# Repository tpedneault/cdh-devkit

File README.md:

# Define the color scheme
set colors(bg) "#ECEFF4"
set colors(bg_secondary) "#E5E9F0"
set colors(bg_highlight) "#D8DEE9"
set colors(fg) "#2E3440"
set colors(fg_secondary) "#3B4252"
set colors(fg_highlight) "#4C566A"
set colors(accent) "#5E81AC"
set colors(accent_hover) "#81A1C1"
set colors(accent_active) "#88C0D0"
set colors(border) "#D8DEE9"
set colors(border_focus) "#5E81AC"
set colors(border_disabled) "#E5E9F0"
set colors(button_bg) "#88C0D0"
set colors(button_fg) "#2E3440"
set colors(button_hover_bg) "#81A1C1"
set colors(button_active_bg) "#5E81AC"
set colors(input_bg) "#E5E9F0"
set colors(input_fg) "#2E3440"
set colors(input_border) "#D8DEE9"
set colors(alert_success_bg) "#A3BE8C"
set colors(alert_success_fg) "#2E3440"
set colors(alert_warning_bg) "#EBCB8B"
set colors(alert_warning_fg) "#2E3440"
set colors(alert_error_bg) "#BF616A"
set colors(alert_error_fg) "#2E3440"

# Create the main window
ttk::style configure TFrame -background $colors(bg)
ttk::style configure TLabel -background $colors(bg) -foreground $colors(fg)
ttk::style configure TButton -background $colors(button_bg) -foreground $colors(button_fg) -padding 6 -relief flat
ttk::style map TButton -background {active $colors(button_active_bg) pressed $colors(button_active_bg) focus $colors(accent_active)}
ttk::style configure TEntry -fieldbackground $colors(input_bg) -foreground $colors(input_fg) -relief solid -padding 6
ttk::style configure TCheckbutton -background $colors(bg) -foreground $colors(fg)
ttk::style configure TRadiobutton -background $colors(bg) -foreground $colors(fg)
ttk::style configure TCombobox -fieldbackground $colors(input_bg) -foreground $colors(input_fg) -relief solid -padding 6
ttk::style configure TSpinbox -fieldbackground $colors(input_bg) -foreground $colors(input_fg) -relief solid -padding 6
ttk::style configure TLabelframe -background $colors(bg) -foreground $colors(fg) -padding 10
ttk::style configure TLabelframe.Label -background $colors(bg) -foreground $colors(fg)
ttk::style configure Treeview -background $colors(bg_secondary) -foreground $colors(fg) -fieldbackground $colors(bg_secondary)
ttk::style configure Treeview.Heading -background $colors(bg_highlight) -foreground $colors(fg_highlight)
ttk::style configure TNotebook -background $colors(bg)
ttk::style configure TNotebook.Tab -background $colors(bg) -foreground $colors(fg)
ttk::style configure Horizontal.TScrollbar -background $colors(border)
ttk::style configure Vertical.TScrollbar -background $colors(border)
ttk::style configure TProgressbar -background $colors(accent)
ttk::style configure TSeparator -background $colors(border)
ttk::style configure TSizegrip -background $colors(bg_secondary)

# Create a sample GUI
ttk::frame .frame -padding "10 10 10 10"
grid .frame -column 0 -row 0 -sticky "nwes"

ttk::label .frame.label -text "Hello, World!"
grid .frame.label -column 0 -row 0 -pady 5

ttk::button .frame.button -text "Click Me"
grid .frame.button -column 0 -row 1 -pady 5

ttk::entry .frame.entry
grid .frame.entry -column 0 -row 2 -pady 5

ttk::checkbutton .frame.check -text "Check Me"
grid .frame.check -column 0 -row 3 -pady 5

ttk::radiobutton .frame.radio -text "Option 1" -value 1 -variable option
grid .frame.radio -column 0 -row 4 -pady 5

ttk::combobox .frame.combo -values {Option1 Option2 Option3}
grid .frame.combo -column 0 -row 5 -pady 5

ttk::spinbox .frame.spin -from 0 -to 10
grid .frame.spin -column 0 -row 6 -pady 5

ttk::labelframe .frame.labelframe -text "Group"
grid .frame.labelframe -column 0 -row 7 -pady 5

ttk::notebook .frame.notebook
grid .frame.notebook -column 0 -row 8 -pady 5

ttk::treeview .frame.tree -columns {Name Age}
grid .frame.tree -column 0 -row 9 -pady 5

ttk::progressbar .frame.progress
grid .frame.progress -column 0 -row 10 -pady 5

# Add contents to the labelframe
ttk::label .frame.labelframe.label -text "Inside Group"
grid .frame.labelframe.label -column 0 -row 0 -pady 5

# Add tabs to the notebook
ttk::frame .frame.notebook.tab1
ttk::frame .frame.notebook.tab2
.frame.notebook add .frame.notebook.tab1 -text "Tab 1"
.frame.notebook add .frame.notebook.tab2 -text "Tab 2"

# Add items to the treeview
.frame.tree heading Name -text "Name"
.frame.tree heading Age -text "Age"
.frame.tree insert {} end -values {"Alice" 30}
.frame.tree insert {} end -values {"Bob" 25}

# Start the main loop
tk::mainloop

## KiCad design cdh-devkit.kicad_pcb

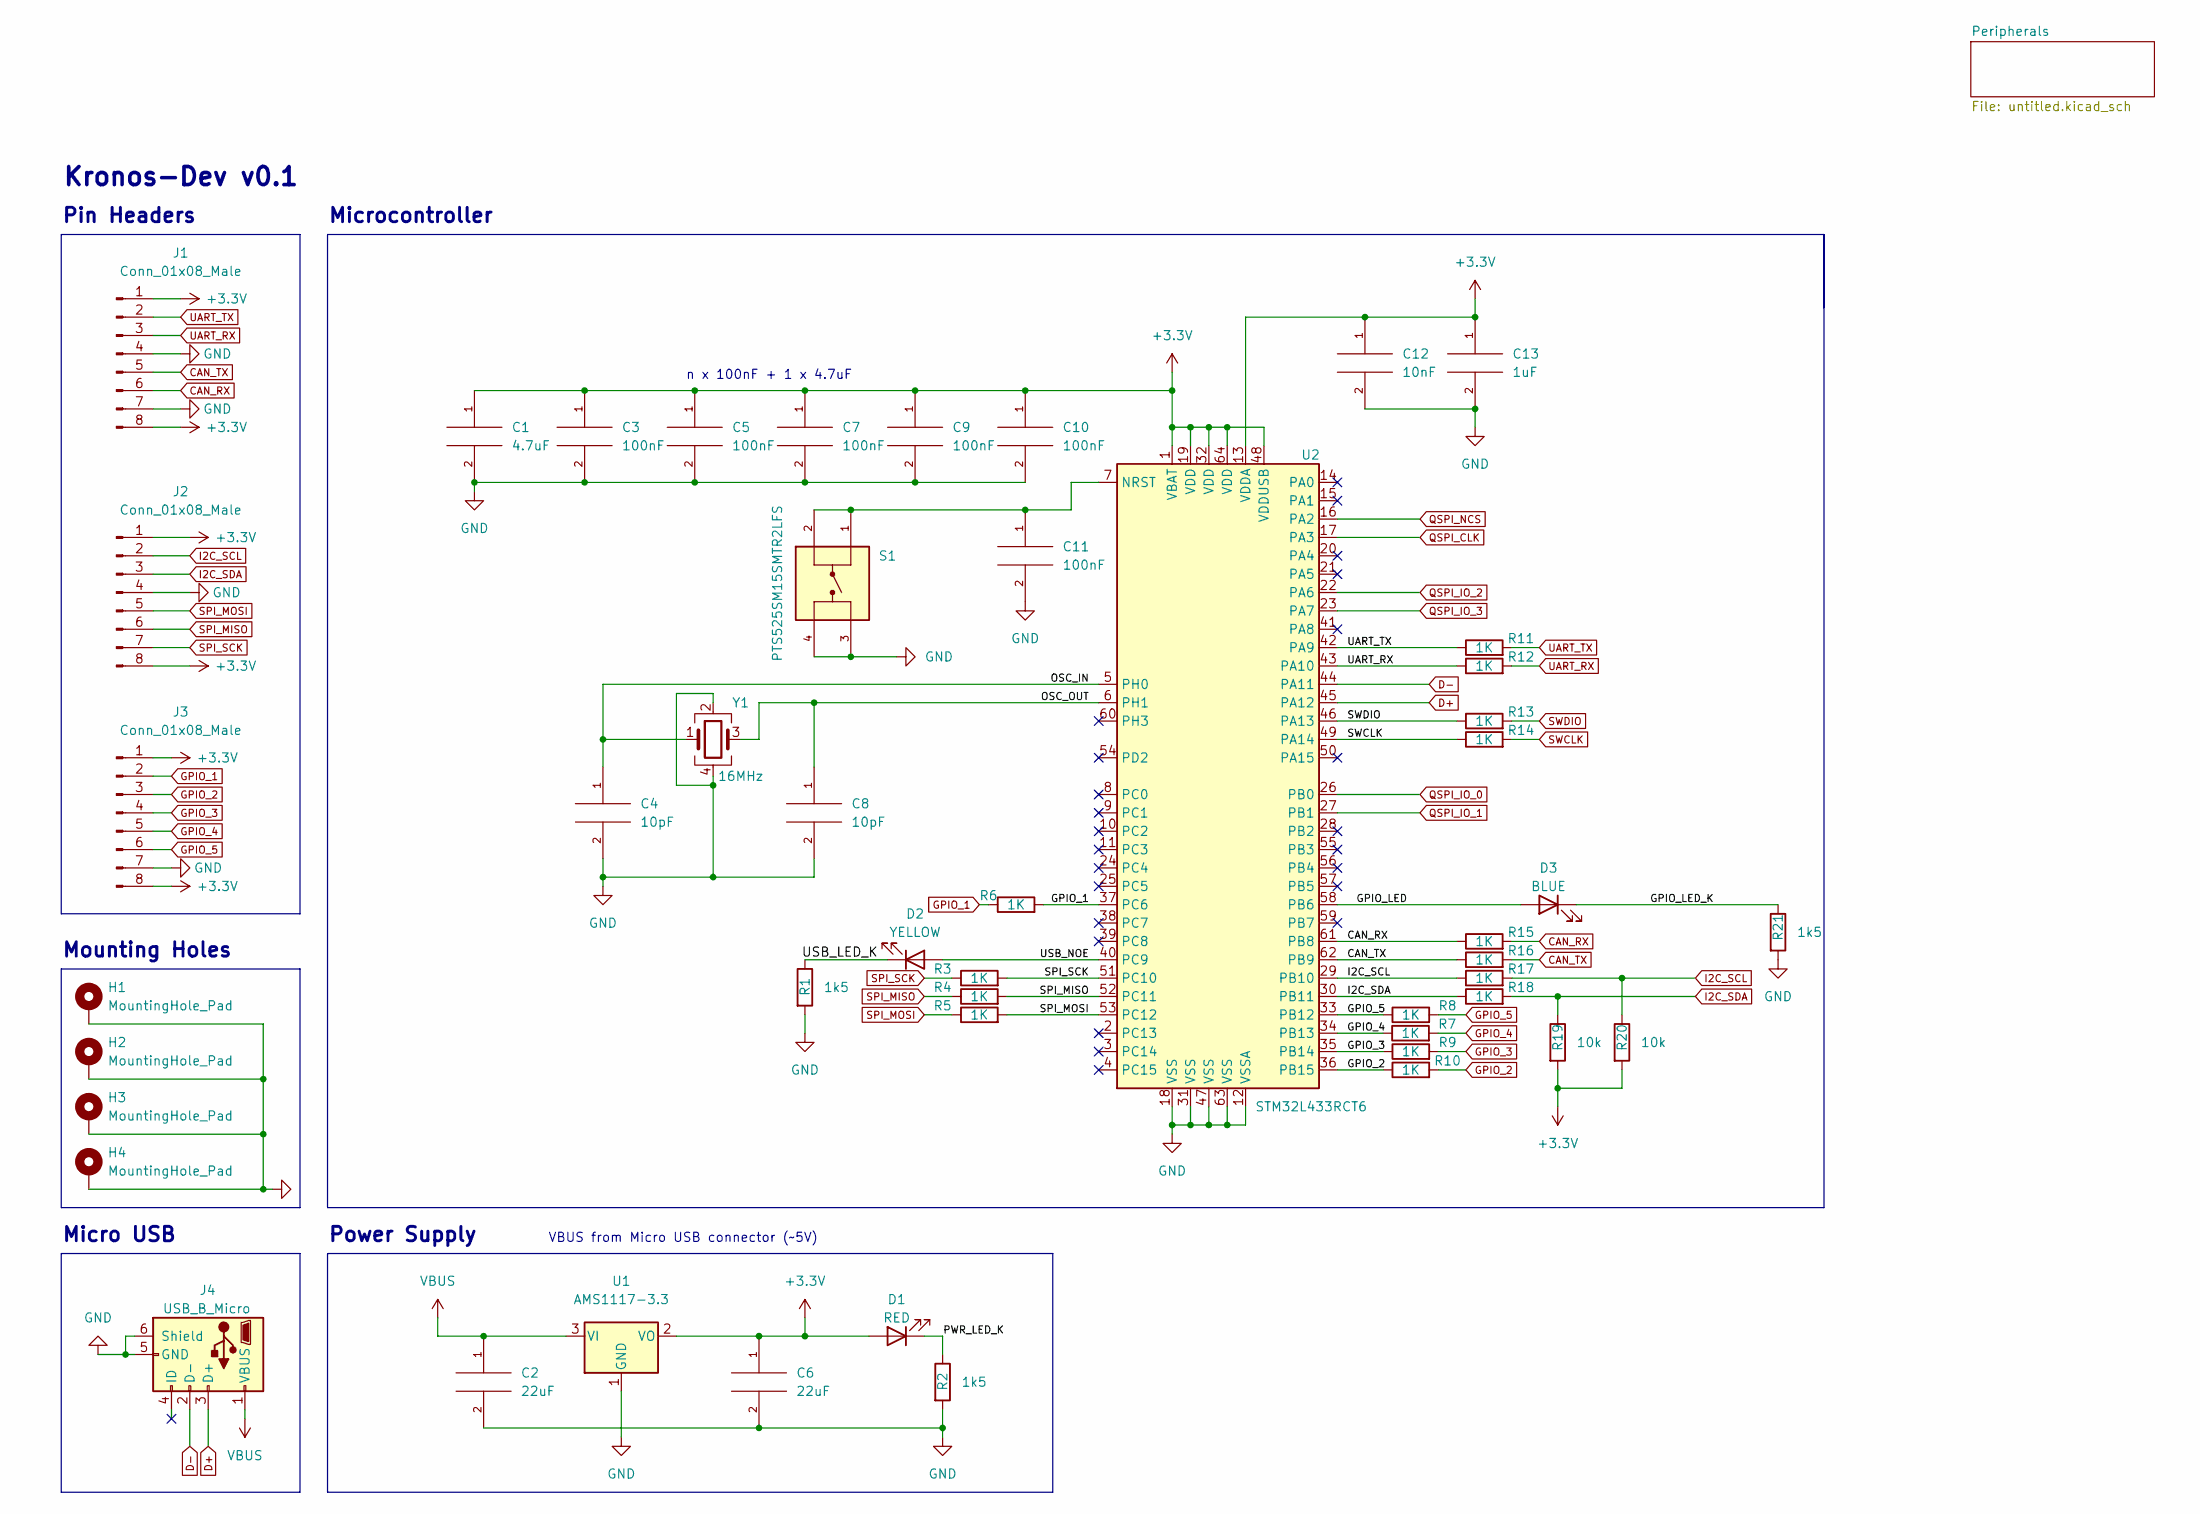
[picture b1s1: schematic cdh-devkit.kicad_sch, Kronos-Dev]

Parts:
C1: 4.7uF; C_0603_1608Metric
C2, C6: 22uF; C_0805_2012Metric
C3, C5, C7, C9, C10, C11: 100nF; C_0402_1005Metric
C4, C8: 10pF; C_0402_1005Metric
C12: 10nF; C_0402_1005Metric
C13: 1uF; C_0402_1005Metric
D1: RED; LED_0603_1608Metric
D2: YELLOW; LED_0603_1608Metric
D3: BLUE; LED_0603_1608Metric
H1, H2, H3, H4: MountingHole_Pad; MountingHole_2.2mm_M2_Pad
J1, J2, J3: Conn_01x08_Male; PinHeader_1x08_P2.54mm_Vertical
J4: USB_B_Micro; USB_Micro-B_Molex-105017-0001
R1, R2, R21: 1k5; R_0402_1005Metric
R3, R4, R5, R6, R7, R8, R9, R10, R11, R12, R13, R14, R15, R16, R17, R18: 1K; R_0402_1005Metric
R19, R20: 10k; R_0402_1005Metric
S1: PTS525SM15SMTR2LFS; SW_PTS525SM15SMTR2LFS; PARTREV NA
U1: AMS1117-3.3; SOT-223-3_TabPin2
U2: STM32L433RCT6; LQFP-64_10x10mm_P0.5mm
Y1: 16MHz; Crystal_SMD_3225-4Pin_3.2x2.5mm

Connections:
+3.3V: C1.1, C3.1, C5.1, C6.1, C7.1, C9.1, C10.1, C12.1, C13.1, D1.2 (A), J1.1, J1.8, J2.1, J2.8, J3.1, J3.8, R19.2, R20.2, U1.2 (VO), U2.1 (VBAT), U2.13 (VDDA), U2.19 (VDD), U2.32 (VDD), U2.48 (VDDUSB), U2.64 (VDD); also elsewhere on the board
/GPIO_LED: D3.2 (A), U2.58 (PB6)
/GPIO_LED_K: D3.1 (K), R21.1
/OSC_IN: C4.1, U2.5 (PH0), Y1.1
/OSC_OUT: C8.1, U2.6 (PH1), Y1.3
/PWR_LED_K: D1.1 (K), R2.1
/USB_LED_K: D2.1 (K), R1.1
/USB_NOE: D2.2 (A), U2.40 (PC9)
CAN_RX: J1.6, R15.1, R15.2, U2.61 (PB8); also elsewhere on the board
CAN_TX: J1.5, R16.1, R16.2, U2.62 (PB9); also elsewhere on the board
D+: J4.3 (D+), U2.45 (PA12); also elsewhere on the board
D-: J4.2 (D-), U2.44 (PA11); also elsewhere on the board
GND: C1.2, C2.2, C3.2, C4.2, C5.2, C6.2, C7.2, C8.2, C9.2, C10.2, C11.2, C12.2, C13.2, H1.1, H2.1, H3.1, H4.1, J1.4, J1.7, J2.4, J3.7, J4.5 (GND), J4.6 (Shield), R1.2, R2.2, R21.2, S1.3, S1.4, U1.1 (GND), U2.12 (VSSA), U2.18 (VSS), U2.31 (VSS), U2.47 (VSS), U2.63 (VSS), Y1.2, Y1.4; also elsewhere on the board
GPIO_1: J3.2, R6.1, R6.2, U2.37 (PC6); also elsewhere on the board
GPIO_2: J3.3, R10.1, R10.2, U2.36 (PB15); also elsewhere on the board
GPIO_3: J3.4, R9.1, R9.2, U2.35 (PB14); also elsewhere on the board
GPIO_4: J3.5, R7.1, R7.2, U2.34 (PB13); also elsewhere on the board
GPIO_5: J3.6, R8.1, R8.2, U2.33 (PB12); also elsewhere on the board
I2C_SCL: J2.2, R17.1, R17.2, R20.1, U2.29 (PB10); also elsewhere on the board
I2C_SDA: J2.3, R18.1, R18.2, R19.1, U2.30 (PB11); also elsewhere on the board
unnamed: C11.1, S1.1, S1.2, U2.7 (NRST)
QSPI_CLK: U2.17 (PA3); also elsewhere on the board
QSPI_IO_0: U2.26 (PB0); also elsewhere on the board
QSPI_IO_1: U2.27 (PB1); also elsewhere on the board
QSPI_IO_2: U2.22 (PA6); also elsewhere on the board
QSPI_IO_3: U2.23 (PA7); also elsewhere on the board
QSPI_NCS: U2.16 (PA2); also elsewhere on the board
SPI_MISO: J2.6, R4.1, R4.2, U2.52 (PC11); also elsewhere on the board
SPI_MOSI: J2.5, R5.1, R5.2, U2.53 (PC12); also elsewhere on the board
SPI_SCK: J2.7, R3.1, R3.2, U2.51 (PC10); also elsewhere on the board
SWCLK: R14.1, R14.2, U2.49 (PA14); also elsewhere on the board
SWDIO: R13.1, R13.2, U2.46 (PA13); also elsewhere on the board
UART_RX: J1.3, R12.1, R12.2, U2.43 (PA10); also elsewhere on the board
UART_TX: J1.2, R11.1, R11.2, U2.42 (PA9); also elsewhere on the board
VBUS: C2.1, J4.1 (VBUS), U1.3 (VI)

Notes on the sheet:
Power Supply
Pin Headers
VBUS from Micro USB connector (~5V)
Micro USB
Kronos-Dev v0.1
Microcontroller
Mounting Holes
n x 100nF + 1 x 4.7uF

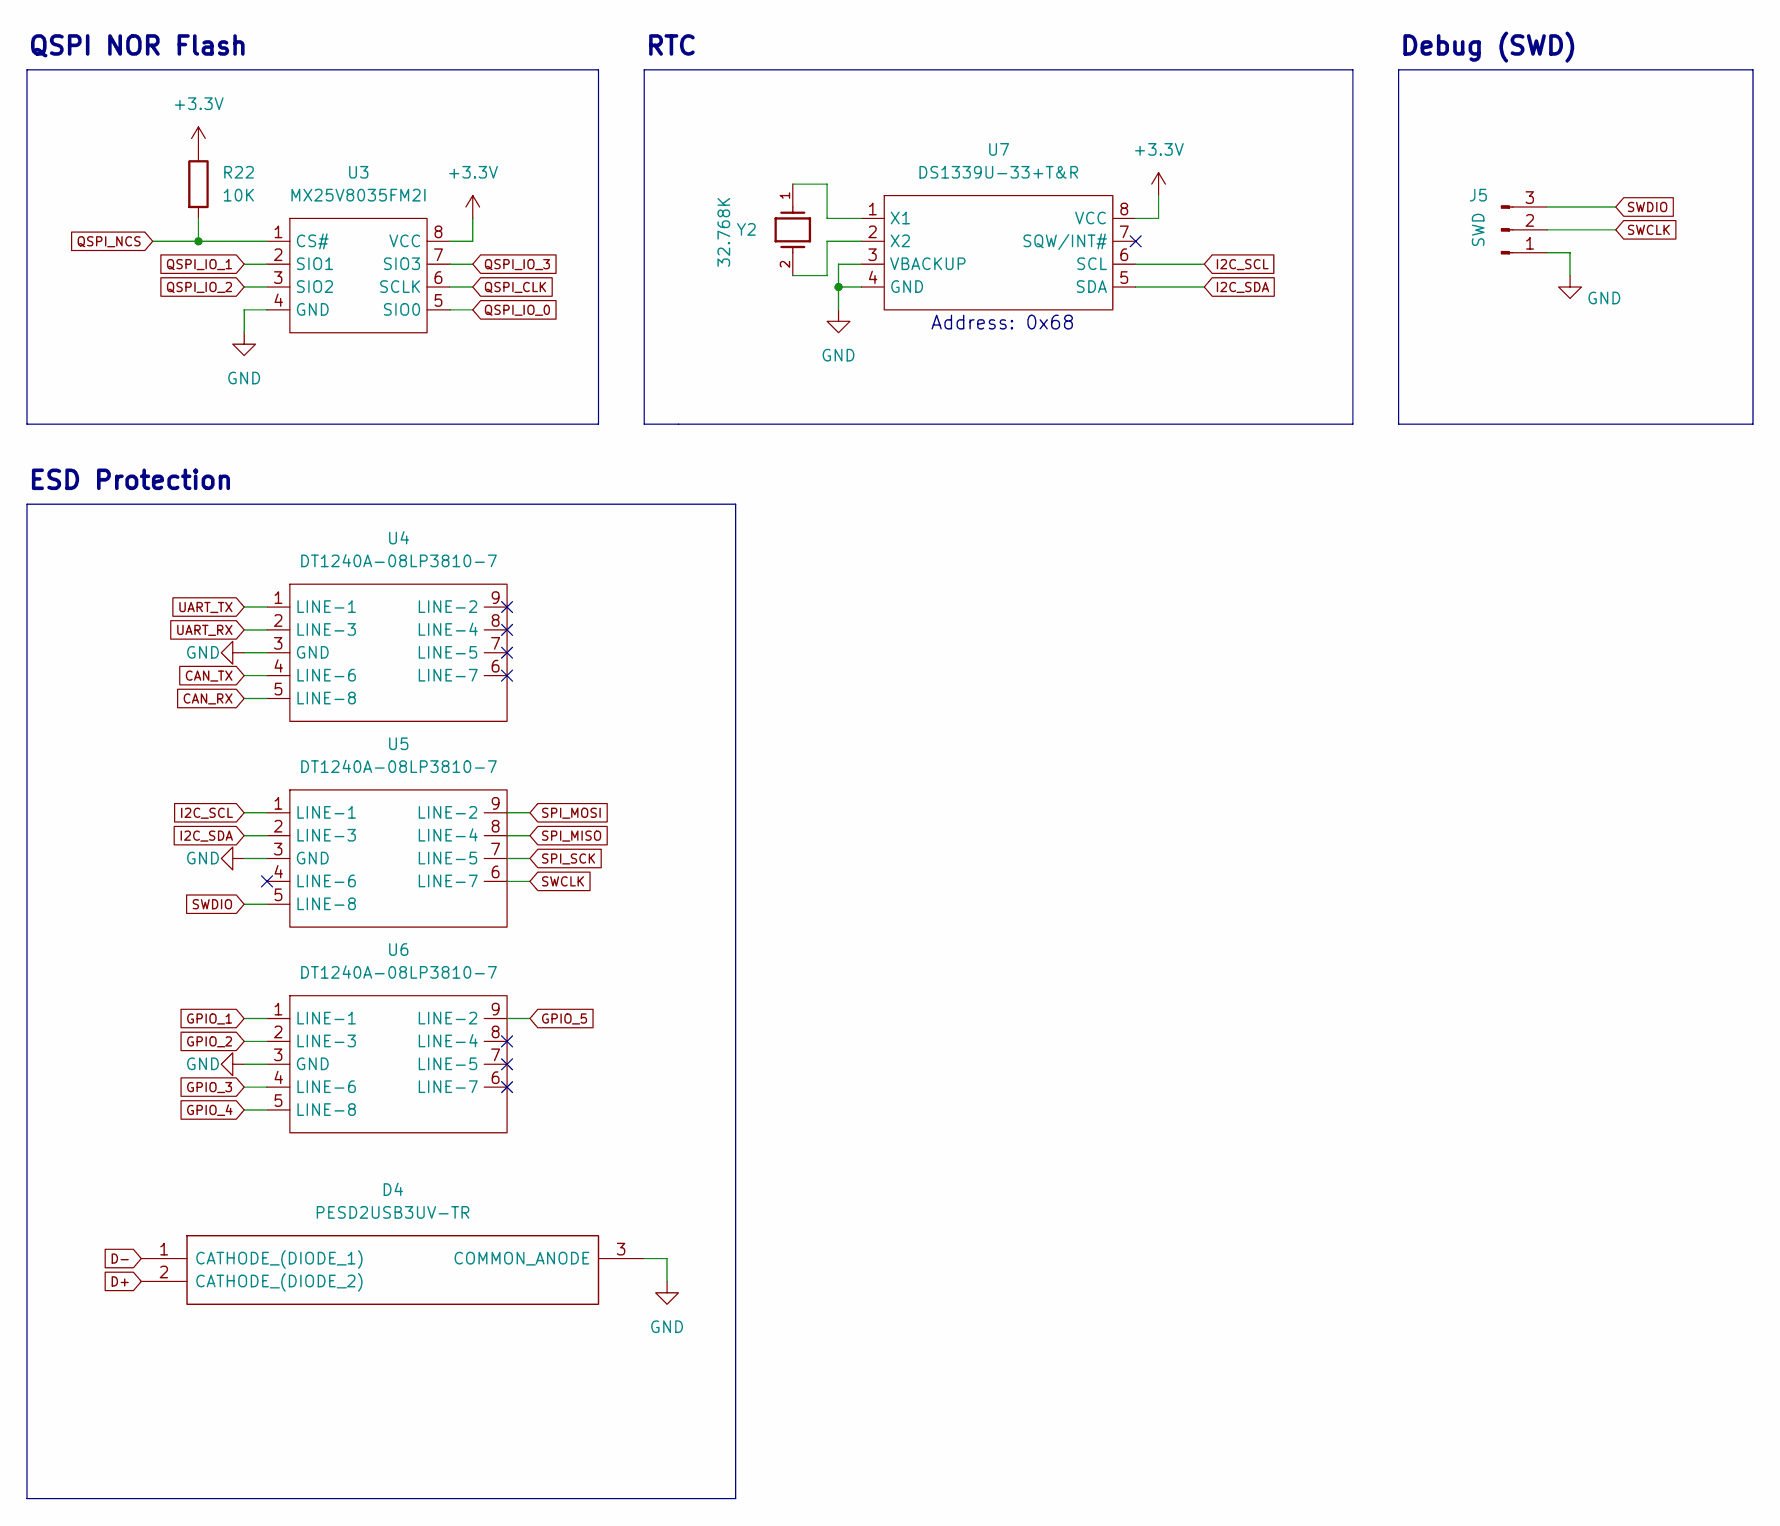
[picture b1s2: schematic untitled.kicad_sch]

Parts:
D4: PESD2USB3UV-TR; SOT95P230X110-3N; Mouser Part Number 771-PESD2USB3UV-TR
J5: SWD; PinHeader_1x03_P2.54mm_Vertical
R22: 10K; R_0603_1608Metric
U3: MX25V8035FM2I; SOIC127P790X216-8N
U4, U5, U6: DT1240A-08LP3810-7; TVS_824014883
U7: DS1339U-33+T&R; 21-0036K
Y2: 32.768K; XTAL_NX3215SA-32.768K-STD-MUA-14; PARTREV --

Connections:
+3.3V: R22.1, U3.8 (VCC), U7.8 (VCC); also elsewhere on the board
CAN_RX: U4.5 (LINE-8); also elsewhere on the board
CAN_TX: U4.4 (LINE-6); also elsewhere on the board
D+: D4.2 (CATHODE_(DIODE_2)); also elsewhere on the board
D-: D4.1 (CATHODE_(DIODE_1)); also elsewhere on the board
GND: D4.3 (COMMON_ANODE), J5.1, U3.4 (GND), U4.3 (GND), U5.3 (GND), U6.3 (GND), U7.3 (VBACKUP), U7.4 (GND); also elsewhere on the board
GPIO_1: U6.1 (LINE-1); also elsewhere on the board
GPIO_2: U6.2 (LINE-3); also elsewhere on the board
GPIO_3: U6.4 (LINE-6); also elsewhere on the board
GPIO_4: U6.5 (LINE-8); also elsewhere on the board
GPIO_5: U6.9 (LINE-2); also elsewhere on the board
I2C_SCL: U5.1 (LINE-1), U7.6 (SCL); also elsewhere on the board
I2C_SDA: U5.2 (LINE-3), U7.5 (SDA); also elsewhere on the board
unnamed: U7.1 (X1), Y2.1
unnamed: U7.2 (X2), Y2.2
QSPI_CLK: U3.6 (SCLK); also elsewhere on the board
QSPI_IO_0: U3.5 (SIO0); also elsewhere on the board
QSPI_IO_1: U3.2 (SIO1); also elsewhere on the board
QSPI_IO_2: U3.3 (SIO2); also elsewhere on the board
QSPI_IO_3: U3.7 (SIO3); also elsewhere on the board
QSPI_NCS: R22.2, U3.1 (CS#); also elsewhere on the board
SPI_MISO: U5.8 (LINE-4); also elsewhere on the board
SPI_MOSI: U5.9 (LINE-2); also elsewhere on the board
SPI_SCK: U5.7 (LINE-5); also elsewhere on the board
SWCLK: J5.2, U5.6 (LINE-7); also elsewhere on the board
SWDIO: J5.3, U5.5 (LINE-8); also elsewhere on the board
UART_RX: U4.2 (LINE-3); also elsewhere on the board
UART_TX: U4.1 (LINE-1); also elsewhere on the board

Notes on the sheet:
Address: 0x68
RTC
Debug (SWD)
ESD Protection
QSPI NOR Flash

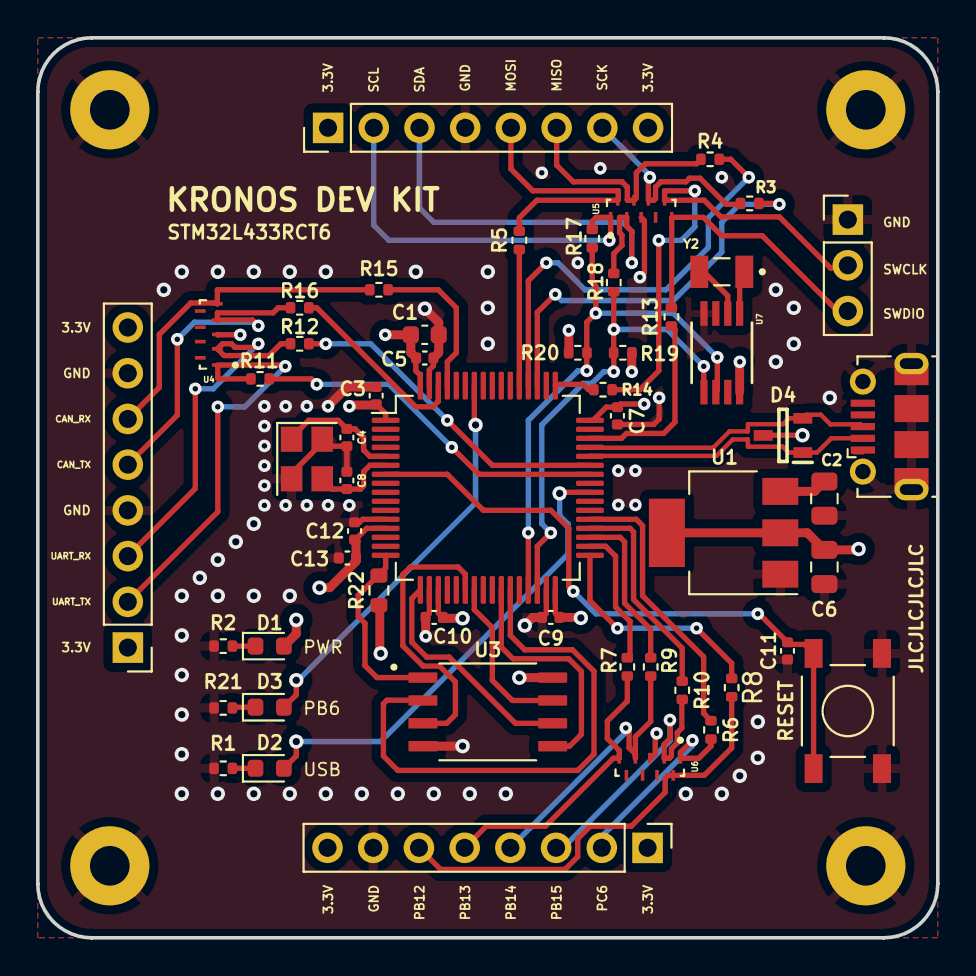
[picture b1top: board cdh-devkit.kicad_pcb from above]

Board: 4 copper layers, 50.0 x 50.0 mm, 58 parts (0 on the bottom side), 37 nets.

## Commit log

2022-11-28 added project files
2022-12-02 version 0.1
2022-12-02 v1 - added missing 3D models
2022-12-03 started rerouting
2022-12-03 updated routes
2022-12-07 finished second revision
